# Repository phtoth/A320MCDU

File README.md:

# A320MCDU
Homemade Airbus A320 MCDU

EN: This project is intended to create a homemade Airbus A320 MCDU (Multi-Function Control and Display Unit). For this, i will use and abuse of the web server provided by the Aerosoft Airbus A320. Here I'll post all the software schema. The other details of the project will be posted on my blog (www.toth.eti.br).

PT-BR: Este projeto destina-se a criar um Airbus A320 MCDU caseiro (Unidade de Controle e Display Multifuncional). Para isso, vou usar e abusar do servidor web fornecido pelo Aerosoft Airbus A320. Aqui vou postar todo o esquema do software. Os outros detalhes do projeto serão postados no meu blog (www.toth.eti.br).

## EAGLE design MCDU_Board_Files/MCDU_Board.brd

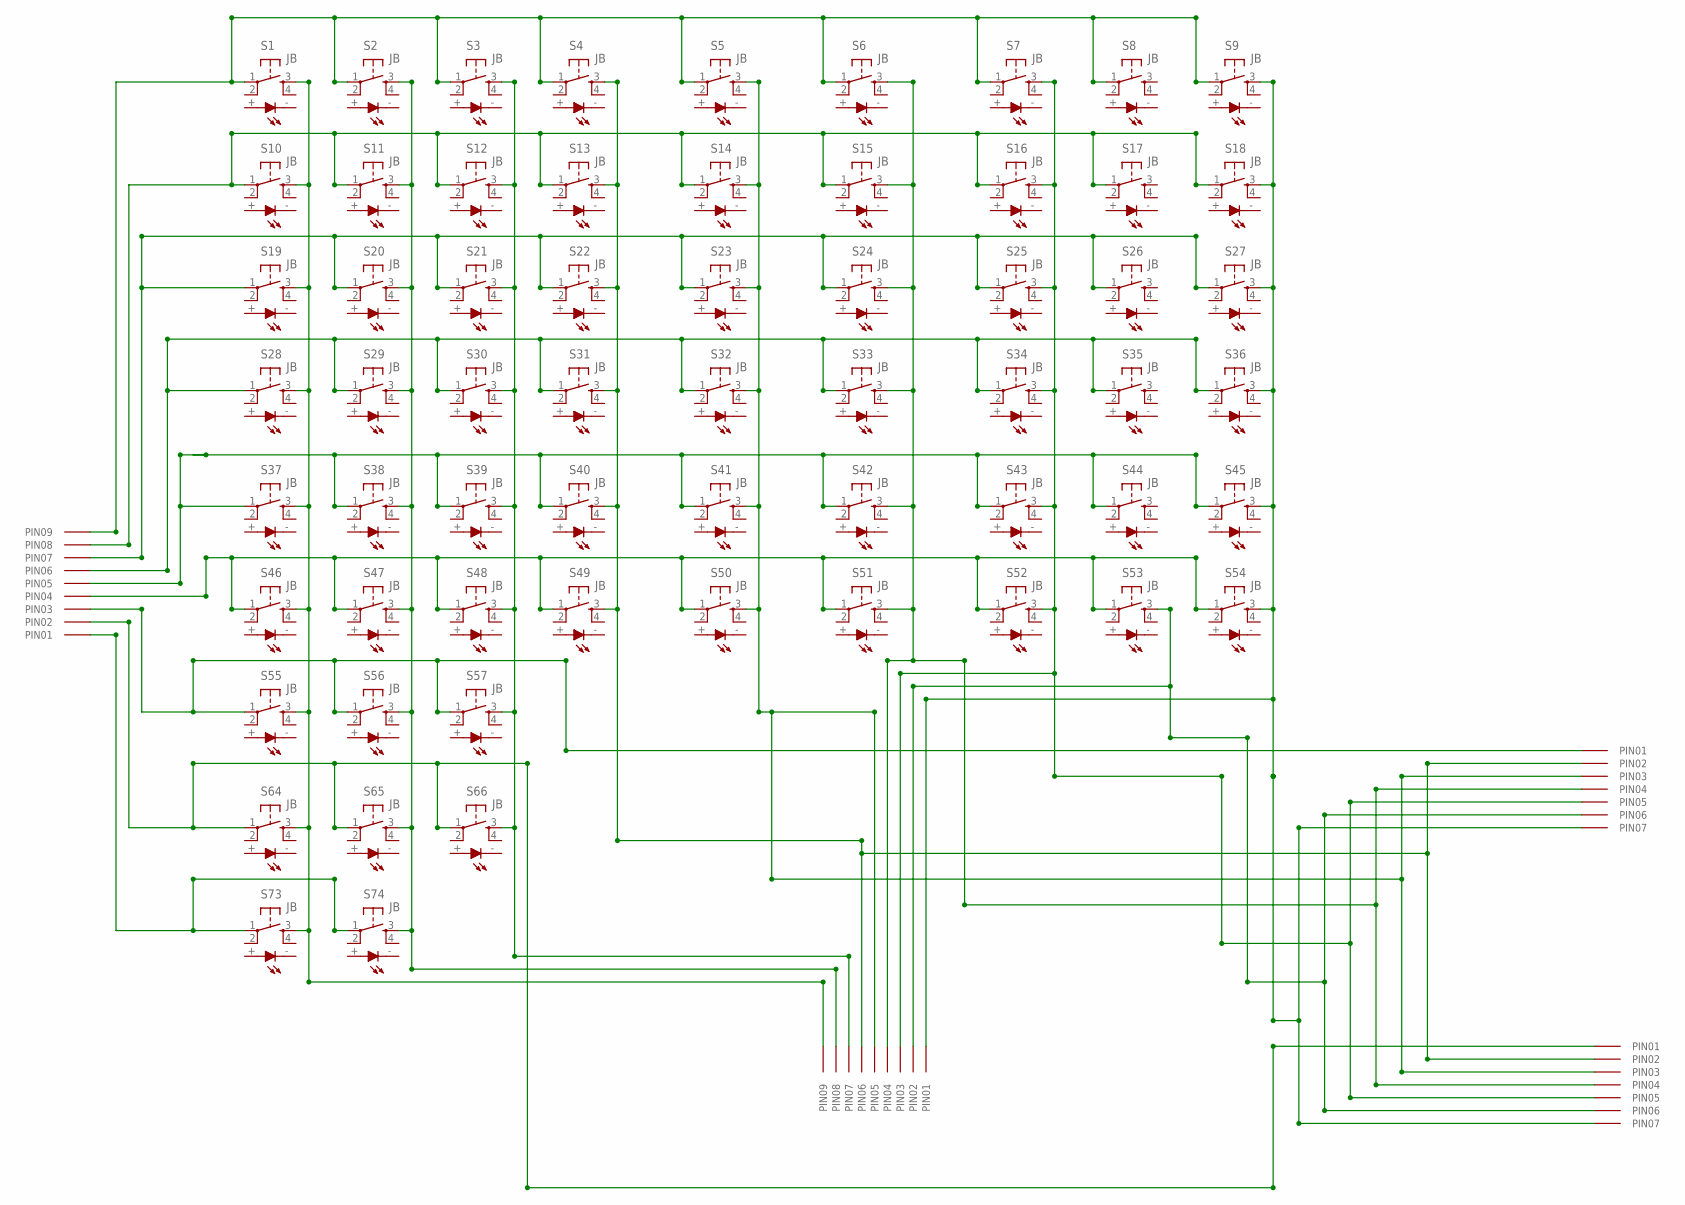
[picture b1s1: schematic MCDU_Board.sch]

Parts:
S1, S2, S3, S4, S5, S6, S7, S8, S9, S10, S11, S12, S13, S14, S15, S16, S17, S18, S19, S20, S21, S22, S23, S24, S25, S26, S27, S28, S29, S30, S31, S32, S33, S34, S35, S36, S37, S38, S39, S40, S41, S42, S43, S44, S45, S46, S47, S48, S49, S50, S51, S52, S53, S54, S55, S56, S57, S64, S65, S66, S73, S74: JB
U$1, U$4: 09PINOS
U$2, U$3: 07PINOS

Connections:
unnamed: S1.1, S2.1, S3.1, S4.1, S5.1, S6.1, S7.1, S8.1, S9.1, U$1.PIN09
unnamed: S10.1, S11.1, S12.1, S13.1, S14.1, S15.1, S16.1, S17.1, S18.1, U$1.PIN08
unnamed: S19.1, S20.1, S21.1, S22.1, S23.1, S24.1, S25.1, S26.1, S27.1, U$1.PIN07
unnamed: S28.1, S29.1, S30.1, S31.1, S32.1, S33.1, S34.1, S35.1, S36.1, U$1.PIN06
unnamed: S37.1, S38.1, S39.1, S40.1, S41.1, S42.1, S43.1, S44.1, S45.1, U$1.PIN05
unnamed: S46.1, S47.1, S48.1, S49.1, S50.1, S51.1, S52.1, S53.1, S54.1, U$1.PIN04
unnamed: S1.3 (S), S10.3 (S), S19.3 (S), S28.3 (S), S37.3 (S), S46.3 (S), S55.3 (S), S64.3 (S), S73.3 (S), U$4.PIN09
unnamed: S73.1, S74.1, U$1.PIN01
unnamed: S2.3 (S), S11.3 (S), S20.3 (S), S29.3 (S), S38.3 (S), S47.3 (S), S56.3 (S), S65.3 (S), S74.3 (S), U$4.PIN08
unnamed: S3.3 (S), S12.3 (S), S21.3 (S), S30.3 (S), S39.3 (S), S48.3 (S), S57.3 (S), S66.3 (S), U$4.PIN07
unnamed: S4.3 (S), S13.3 (S), S22.3 (S), S31.3 (S), S40.3 (S), S49.3 (S), U$2.PIN02, U$3.PIN02, U$4.PIN06
unnamed: S5.3 (S), S14.3 (S), S23.3 (S), S32.3 (S), S41.3 (S), S50.3 (S), U$2.PIN03, U$3.PIN03, U$4.PIN05
unnamed: S7.3 (S), S16.3 (S), S25.3 (S), S34.3 (S), S43.3 (S), S52.3 (S), U$2.PIN05, U$3.PIN05, U$4.PIN03
unnamed: S53.3 (S), U$2.PIN06, U$3.PIN06, U$4.PIN02
unnamed: S9.3 (S), S18.3 (S), S27.3 (S), S36.3 (S), S45.3 (S), S54.3 (S), U$2.PIN07, U$3.PIN07, U$4.PIN01
unnamed: S64.1, S65.1, S66.1, U$1.PIN02, U$3.PIN01
unnamed: S6.3 (S), S15.3 (S), S24.3 (S), S33.3 (S), S42.3 (S), S51.3 (S), U$2.PIN04, U$3.PIN04, U$4.PIN04
unnamed: S55.1, S56.1, S57.1, U$1.PIN03, U$2.PIN01

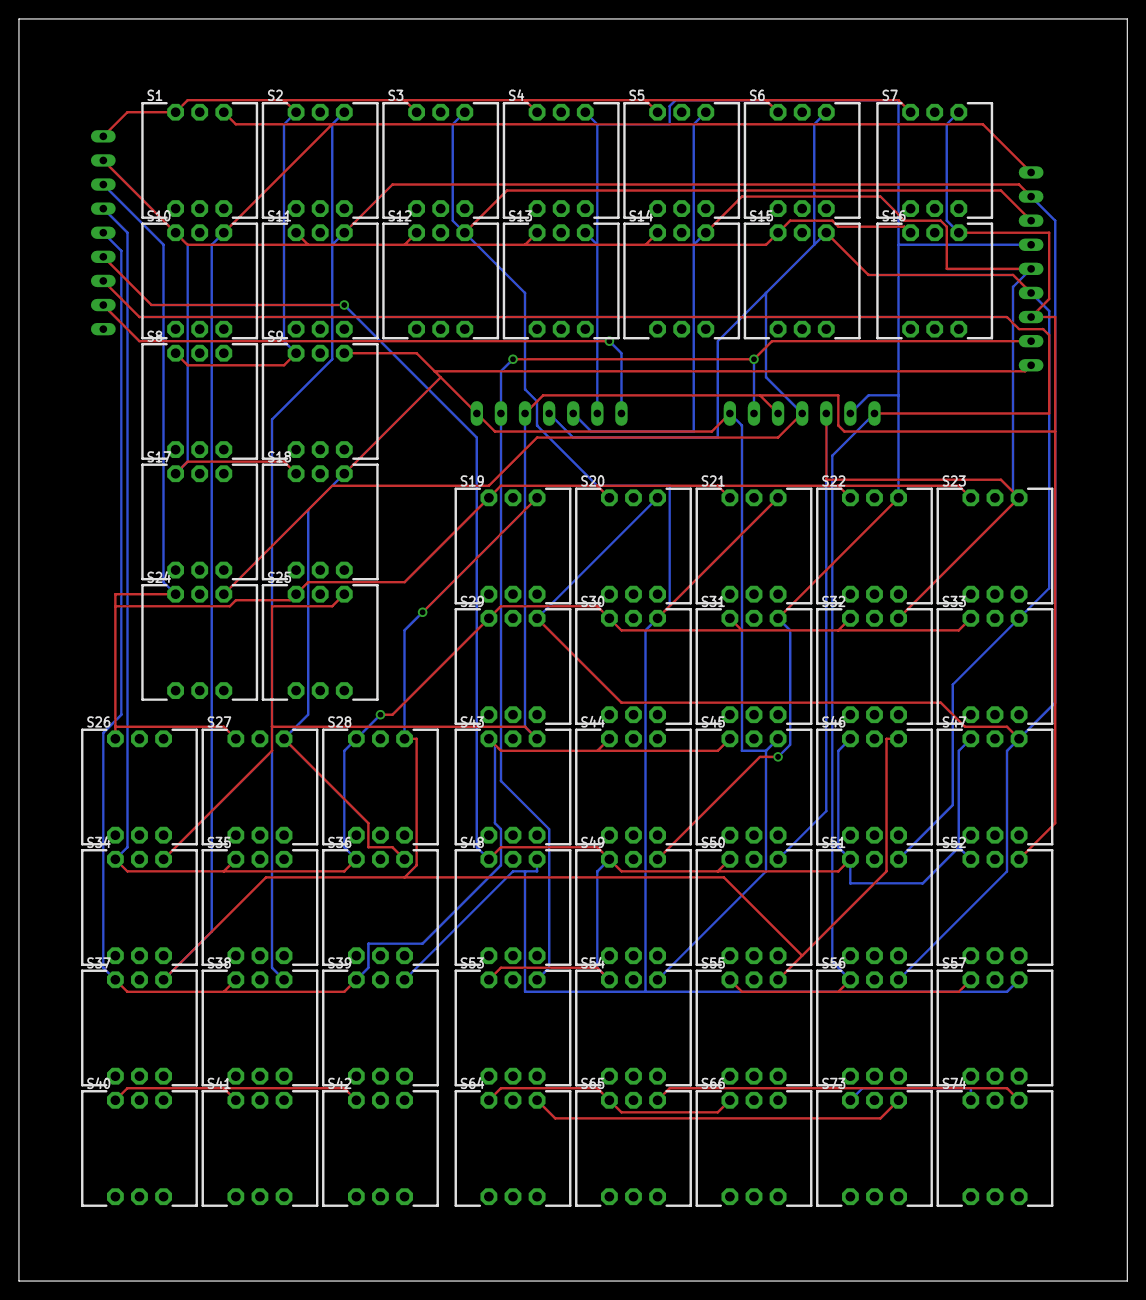
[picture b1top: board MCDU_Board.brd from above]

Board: 2 copper layers, 116.8 x 133.0 mm, 66 parts (0 on the bottom side), 18 nets.

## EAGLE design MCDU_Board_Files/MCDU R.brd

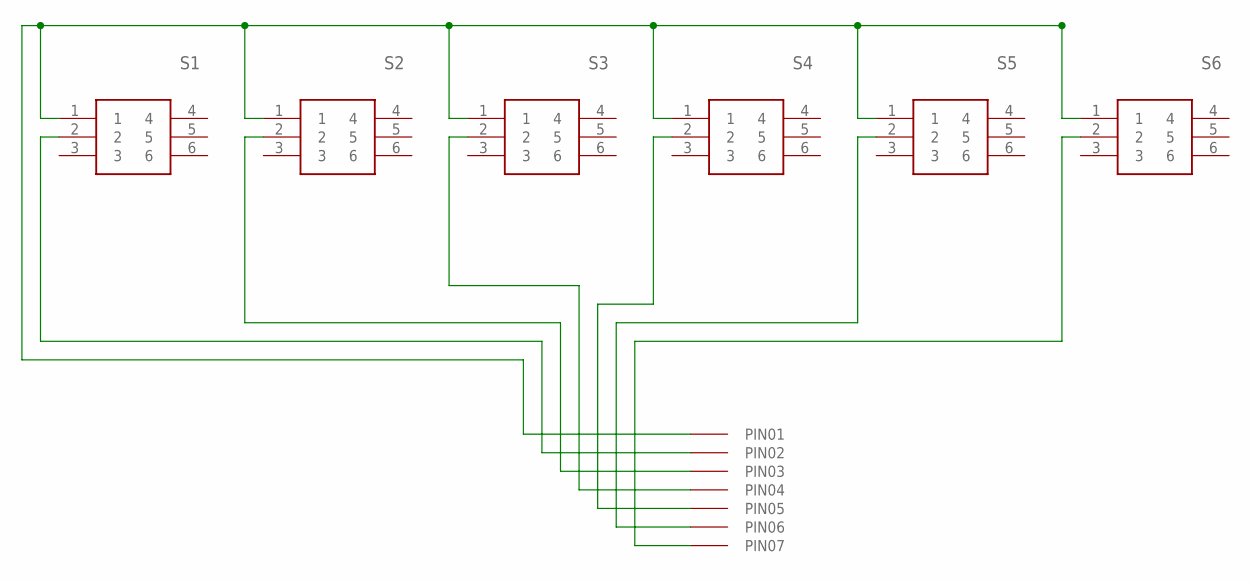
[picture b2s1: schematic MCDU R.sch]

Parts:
S1, S2, S3, S4, S5, S6: PVA2EEH1_1.7NV2; PVA2
U$1: 07PINOS

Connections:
unnamed: S1.1, S2.1, S3.1, S4.1, S5.1, S6.1, U$1.PIN01
unnamed: S6.2, U$1.PIN07
unnamed: S3.2, U$1.PIN04
unnamed: S2.2, U$1.PIN03
unnamed: S4.2, U$1.PIN05
unnamed: S1.2, U$1.PIN02
unnamed: S5.2, U$1.PIN06

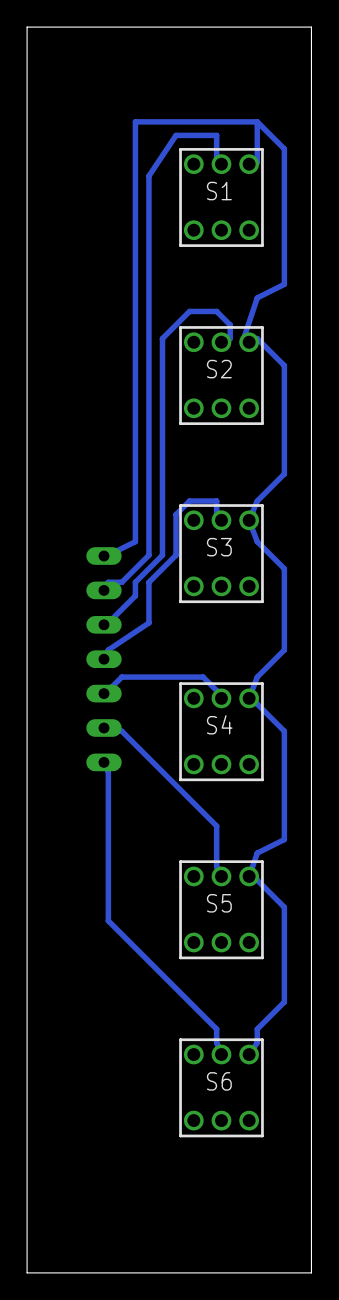
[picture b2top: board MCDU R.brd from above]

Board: 2 copper layers, 21.0 x 92.0 mm, 7 parts (0 on the bottom side), 7 nets.

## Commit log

2018-07-10 Original Aerosoft Airbus Files
2018-07-10 Project files with my changes
2018-08-01 Add the MCDU Board PCB files
2018-09-21 Python Keyboard Code
2018-09-21 All Buttons Working

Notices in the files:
parts and their libraries:
switch-nkk: Copyright (C) 2010, Bob Starr
